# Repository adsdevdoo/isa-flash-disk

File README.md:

# ISA Flash Disk

8-битная ISA-карта с флеш-диском на микросхемах **Intel 28F008SA** для IBM PC XT, AT, 286, 386 и 486.
Цель — загрузка MS-DOS с карты и запись образа диска из DOS.

- 1 или 2 микросхемы PA28F008SA (PSOP-44) на карту: 1 или 2 Мбайт.
- Окно 8 Кбайт в верхней памяти + регистр банка в портах ввода-вывода.
- Собственный Option ROM: диск через INT 13h, загрузка DOS.
- Аппаратная защита от записи: без перемычки JP1 записать флеш невозможно.
- Логика 74HCT, без микроконтроллера.

## Статус

| Этап | Содержание | Состояние |
|---|---|---|
| 1. Исследование | документация, выбор архитектуры | выполнено |
| 2–3. Схема карты | 1–2 микросхемы, банки, защита записи | схема rev A: ERC 0, нетлист сверен |
| 5. Плата | разводка, DRC, Gerber | **rev B: DRC 0, соответствие схеме 0 расхождений**; от rev A отличается только шелкографией ([CHANGELOG](CHANGELOG.md)) |
| 2. Прототип | изготовление, чтение, адресация, запись | **rev A заказана в JLCPCB 2026-11-15** (5 шт., LeadFree HASL, фаска 45°), ещё не получена |
| 4. Программы | Option ROM, FLINFO/FLREAD/FLWRITE/FLFORMAT/FLTEST, mkdisk | **v1.2, чтение и запись из DOS, формат диска 3 (без потерь при сбое питания), проверка износа FLTEST: 136 проверок в эмуляторе, на железе нет** |

**Статус: инженерный прототип, не испытан в железе.** Заказана rev A, актуальная ревизия — rev B (та же медь, новая
шелкография). Плата 104.14 × 100 мм под планку Keystone 9202,
архив для JLCPCB — [hardware/gerber/](hardware/gerber/), параметры заказа и границы проверки —
[docs/manufacturing.md](docs/manufacturing.md). Схема — [docs/schematic.pdf](docs/schematic.pdf),
проект KiCad 9 — [hardware/kicad/](hardware/kicad/). Покупку и заказ выполняет владелец.

## Настройка переключателей

Переключатель в положении **ON = 0**, OFF = 1. Те же таблицы напечатаны на нижней стороне платы, у каждого
переключателя сверху подписан его бит адреса.

**SW1 — окно памяти 8 Кбайт** (SA19 = SA18 = 1 зашиты на плате)

| Окно | 1 (A13) | 2 (A14) | 3 (A15) | 4 (A16) | 5 (A17) |
|---|---|---|---|---|---|
| C8000h | ON | ON | OFF | ON | ON |
| **CC000h (по умолчанию)** | ON | OFF | OFF | ON | ON |
| D0000h | ON | ON | ON | OFF | ON |
| E0000h | ON | ON | ON | ON | OFF |

**SW2 — порты ввода-вывода** (8 портов; SA9 = 1 зашит, AEN = 0)

| Порты | 1 (A3) | 2 (A4) | 3 (A5) | 4 (A6) | 5 (A7) | 6 (A8) |
|---|---|---|---|---|---|---|
| 280h | ON | ON | ON | ON | OFF | ON |
| **2A0h (по умолчанию)** | ON | ON | OFF | ON | OFF | ON |
| 300h | ON | ON | ON | ON | ON | OFF |

Остальные адреса — по битам: окно C0000h…FE000h с шагом 8 Кбайт, порты 200h…3F8h с шагом 8
([docs/memory-map.md](docs/memory-map.md)). **JP1 WRITE** снята — флеш защищена от записи; ставится только на время
записи утилитами.

## Заказ платы в JLCPCB

Загрузить [hardware/gerber/isa-flash-disk-revB-jlcpcb.zip](hardware/gerber/isa-flash-disk-revB-jlcpcb.zip)
(rev A, заказанная 2026-11-15, лежит рядом без изменений) и выставить в форме:

| Поле | Значение |
|---|---|
| Base Material | FR-4 |
| Layers | 2 |
| Dimensions | 104.14 × 100 мм (определяется само) |
| Delivery Format | Single PCB |
| PCB Thickness | 1.6mm |
| Surface Finish | **LeadFree HASL** для прототипа (ламели лужёные) или **ENIG** (ламели золотые). Не OSP |
| Outer Copper Weight | 1 oz |
| Via Covering | Tented |
| Min via hole size/diameter | 0.3mm/(0.4/0.45mm) |
| Mark on PCB | Remove Mark |
| Gold Fingers | **Yes**, иначе не будет фаски |
| Beveling | **45°** |

Остальное — по умолчанию.

**Почему 45°, а не 30°:** при 30° фаска уходит на 1.13 мм от края (так пишет форма JLCPCB), а ламели
начинаются в 1.0 мм — фаска их заденет. После выбора 45° число d под картинкой должно быть меньше 1.0 мм.

Контур разъёма (выступ и уступы по бокам) уже есть в Gerber, отдельно его заказывать не нужно.

## Документация

| Файл | Что внутри |
|---|---|
| [docs/research.md](docs/research.md) | источники, находки, решения и открытые вопросы этапа 1 |
| [docs/intel-28f008sa.md](docs/intel-28f008sa.md) | характеристики микросхемы со ссылками на страницы даташита |
| [docs/original-module.md](docs/original-module.md) | исходный модуль и снятие микросхем |
| [docs/architecture.md](docs/architecture.md) | сравнение вариантов, выбранная схема, защита, VPP |
| [docs/isa-interface.md](docs/isa-interface.md) | шина ISA: контакты, циклы, питание, Option ROM |
| [docs/memory-map.md](docs/memory-map.md) | адреса окна и портов, регистры, разметка флеш |
| [docs/programming.md](docs/programming.md) | Option ROM, утилиты DOS, первая запись ПЗУ, запись на диск из DOS |
| [docs/testing.md](docs/testing.md) | замеры и проверки |
| [docs/assembly.md](docs/assembly.md) | сборка карты, детали с артикулами LCSC, распечатка платы 1:1 |
| [docs/manufacturing.md](docs/manufacturing.md) | заказ платы в JLCPCB, что проверено |
| [docs/models.md](docs/models.md) | 3D-модели и их ограничения |

Даташиты и руководства IBM лежат в [docs/datasheets/](docs/datasheets/) и [docs/references/](docs/references/).

## Структура

```
docs/          документация, даташиты, руководства
hardware/      kicad/, gerber/, bom/
firmware/      option-rom/ — Option ROM (NASM)
software/      dos/ — утилиты DOS (NASM)
tools/         вспомогательные скрипты для сборки и проверки
```

Документация на русском, исходный код и идентификаторы — на английском.
Рабочие правила проекта — [AGENTS.md](AGENTS.md).

## Лицензия

[MIT](LICENSE). Документы Intel, IBM, TI, AOS, onsemi, Keystone, Kingtek и FH в `docs/datasheets/` и `docs/references/` под эту
лицензию не подпадают и принадлежат их владельцам.

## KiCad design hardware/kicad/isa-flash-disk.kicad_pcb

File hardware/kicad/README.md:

# KiCad

Проект для **KiCad 9.0.2 или новее**: открыть `isa-flash-disk.kicad_pro`.

| Файл | Что это |
|---|---|
| `isa-flash-disk.kicad_sch` | схема rev A, один лист A2 |
| `isa_flash_disk.kicad_sym` | символ Intel 28F008SA (выводы PSOP-44 по DS, рис. 3) |
| `isa_flash_disk.pretty/` | все посадочные места проекта: PSOP-44 по чертежу Intel, ISA 8 бит, копии стандартных KiCad 9 |
| `expected-nets.json` | таблица соединений, из которой построена схема |
| `isa-flash-disk.kicad_pcb` | плата rev B: 104.14 × 100 мм, 2 слоя, разведена, земля залита с двух сторон. Медь как у rev A, изменена шелкография ([CHANGELOG](../../CHANGELOG.md)) |
| `3d/` | 3D-модели всех деталей (копии из KiCad 9.0.2, [docs/models.md](../../docs/models.md)) |
| `reports/erc.rpt` | последний отчёт ERC |
| `reports/netlist-check.txt` | сверка нетлиста с `expected-nets.json` |
| `reports/drc.rpt` | последний DRC платы с проверкой соответствия схеме |

Статус: **схема rev A, плата rev B: ERC 0, DRC 0, соответствие схеме и плате без расхождений. В железе не
проверялось.** PDF схемы — [docs/schematic.pdf](../../docs/schematic.pdf), заказ — [docs/manufacturing.md](../../docs/manufacturing.md).

## Как схема получена

Rev A сгенерирована скриптами:

```bash
python tools/kicad/gen_footprints.py
```

```bash
python tools/kicad/gen_schematic.py
```

Генератор соединяет выводы короткими проводниками с метками цепей, поэтому схема читается как таблица
соединений. Дальше её можно править в KiCad. Генератор не перезапишет схему, изменённую вручную
(сверяет SHA-256 с `.generated.sha256`); `--force` отбрасывает ручные правки.

## Как получена плата

Плата строится в три шага, как в retro535 (размещение скриптом, трассировка FreeRouting, доводка скриптом):

```bash
"C:/Program Files/KiCad/9.0/bin/python.exe" tools/kicad/make_board.py
```

```bash
java -jar freerouting-2.5.0.jar -de hardware/kicad/build/placed.dsn -do hardware/kicad/build/placed.ses -mp 100 --gui.enabled=false
```

```bash
"C:/Program Files/KiCad/9.0/bin/python.exe" tools/kicad/route_board.py
```

- `make_board.py` берёт нетлист из схемы, ставит контур (геометрия под планку Keystone 9202), ламели,
  отверстия под планку, детали, запретную зону на ламелях и зафиксированные отводы от ламелей в тело платы;
  результат — `build/placed.kicad_pcb` и `build/placed.dsn` (папка `build/` не коммитится).
- FreeRouting 2.5.0 — внешний автотрассировщик (github.com/freerouting/freerouting), в репозиторий не входит.
- `route_board.py` импортирует трассировку, заливает землю с двух сторон, добавляет шелкографию и сохраняет
  `isa-flash-disk.kicad_pcb`, переносит правила в `isa-flash-disk.kicad_pro`. Плату, изменённую в KiCad,
  без `--force` не перезаписывает (`.generated-pcb.sha256`).
- Шелкография задана только в `silk_board.py`. `route_board.py` вызывает его до сшивки земли, чтобы
  переходные не попадали под надписи. Отдельно он перерисовывает шелкографию готовой платы, медь не меняет;
  повторный запуск даёт тот же файл:

```bash
"C:/Program Files/KiCad/9.0/bin/python.exe" tools/kicad/silk_board.py
```

  Скрипт ставит обозначения, тип микросхем, транзисторов и резисторных сборок, функциональные подписи,
  нижний информационный блок и таблицы переключателей. Надпись без свободного места или ближе 0.2 мм к
  площадке, 0.15 мм к другой шелкографии — ошибка, а не наложение.

## Проверка после изменений

```bash
kicad-cli sch erc --format report --severity-all -o hardware/kicad/reports/erc.rpt hardware/kicad/isa-flash-disk.kicad_sch
```

```bash
kicad-cli sch export netlist --format kicadsexpr -o netlist.net hardware/kicad/isa-flash-disk.kicad_sch
```

```bash
python tools/kicad/check_netlist.py netlist.net
```

Нетлист содержит абсолютные локальные пути, в репозиторий его не класть.

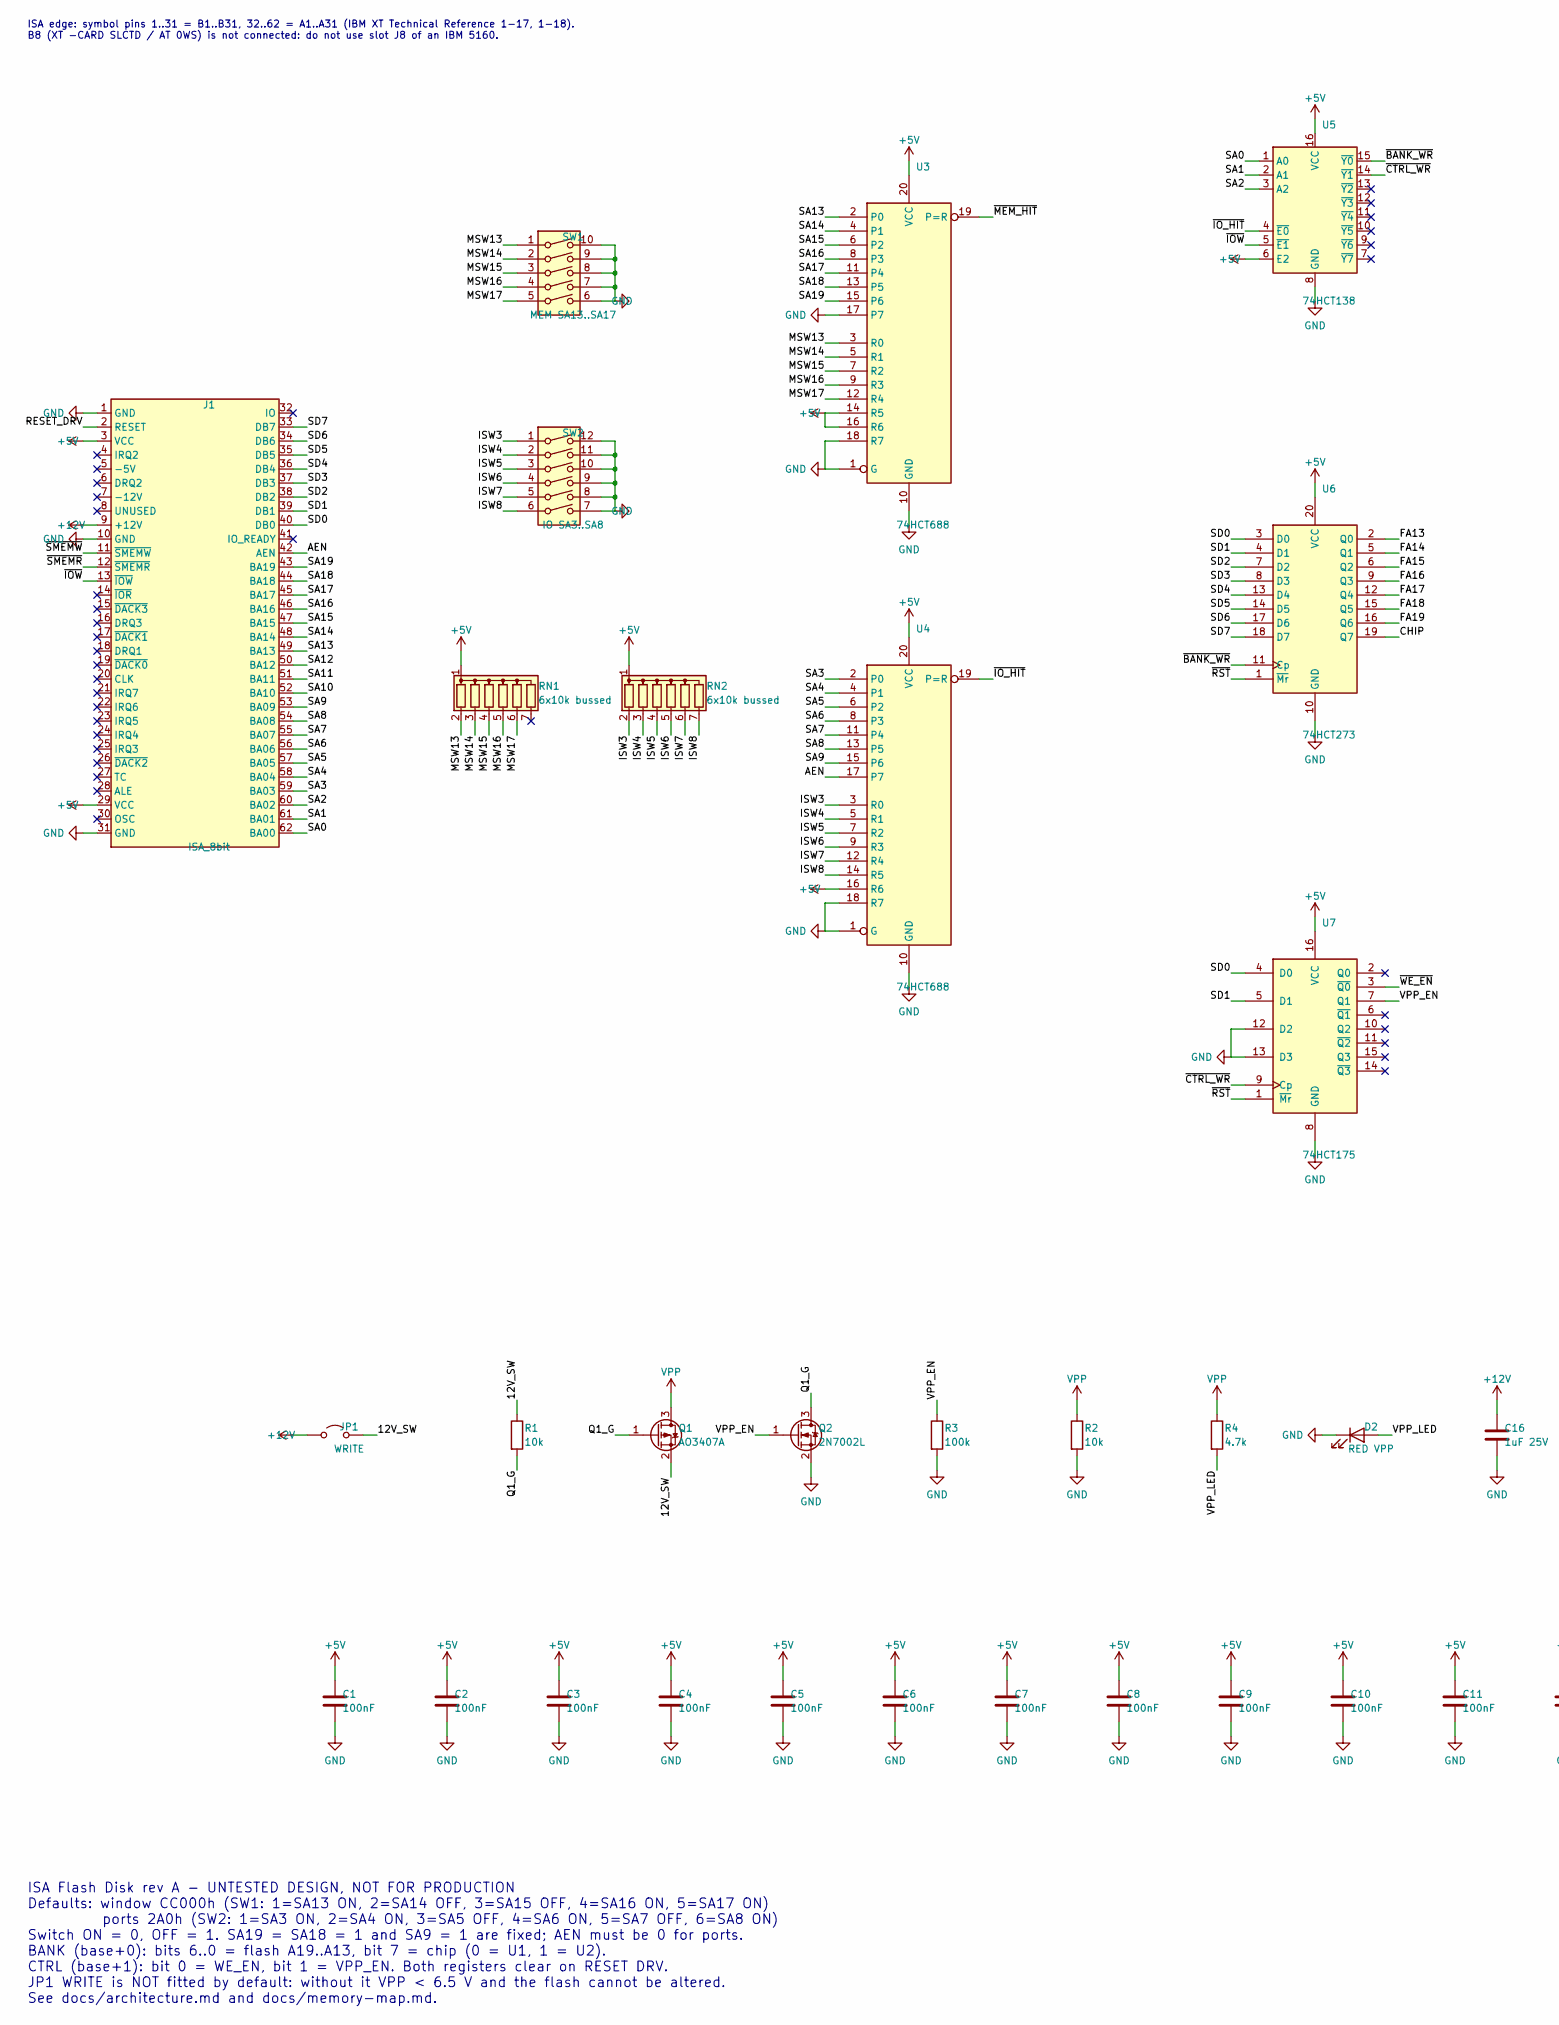
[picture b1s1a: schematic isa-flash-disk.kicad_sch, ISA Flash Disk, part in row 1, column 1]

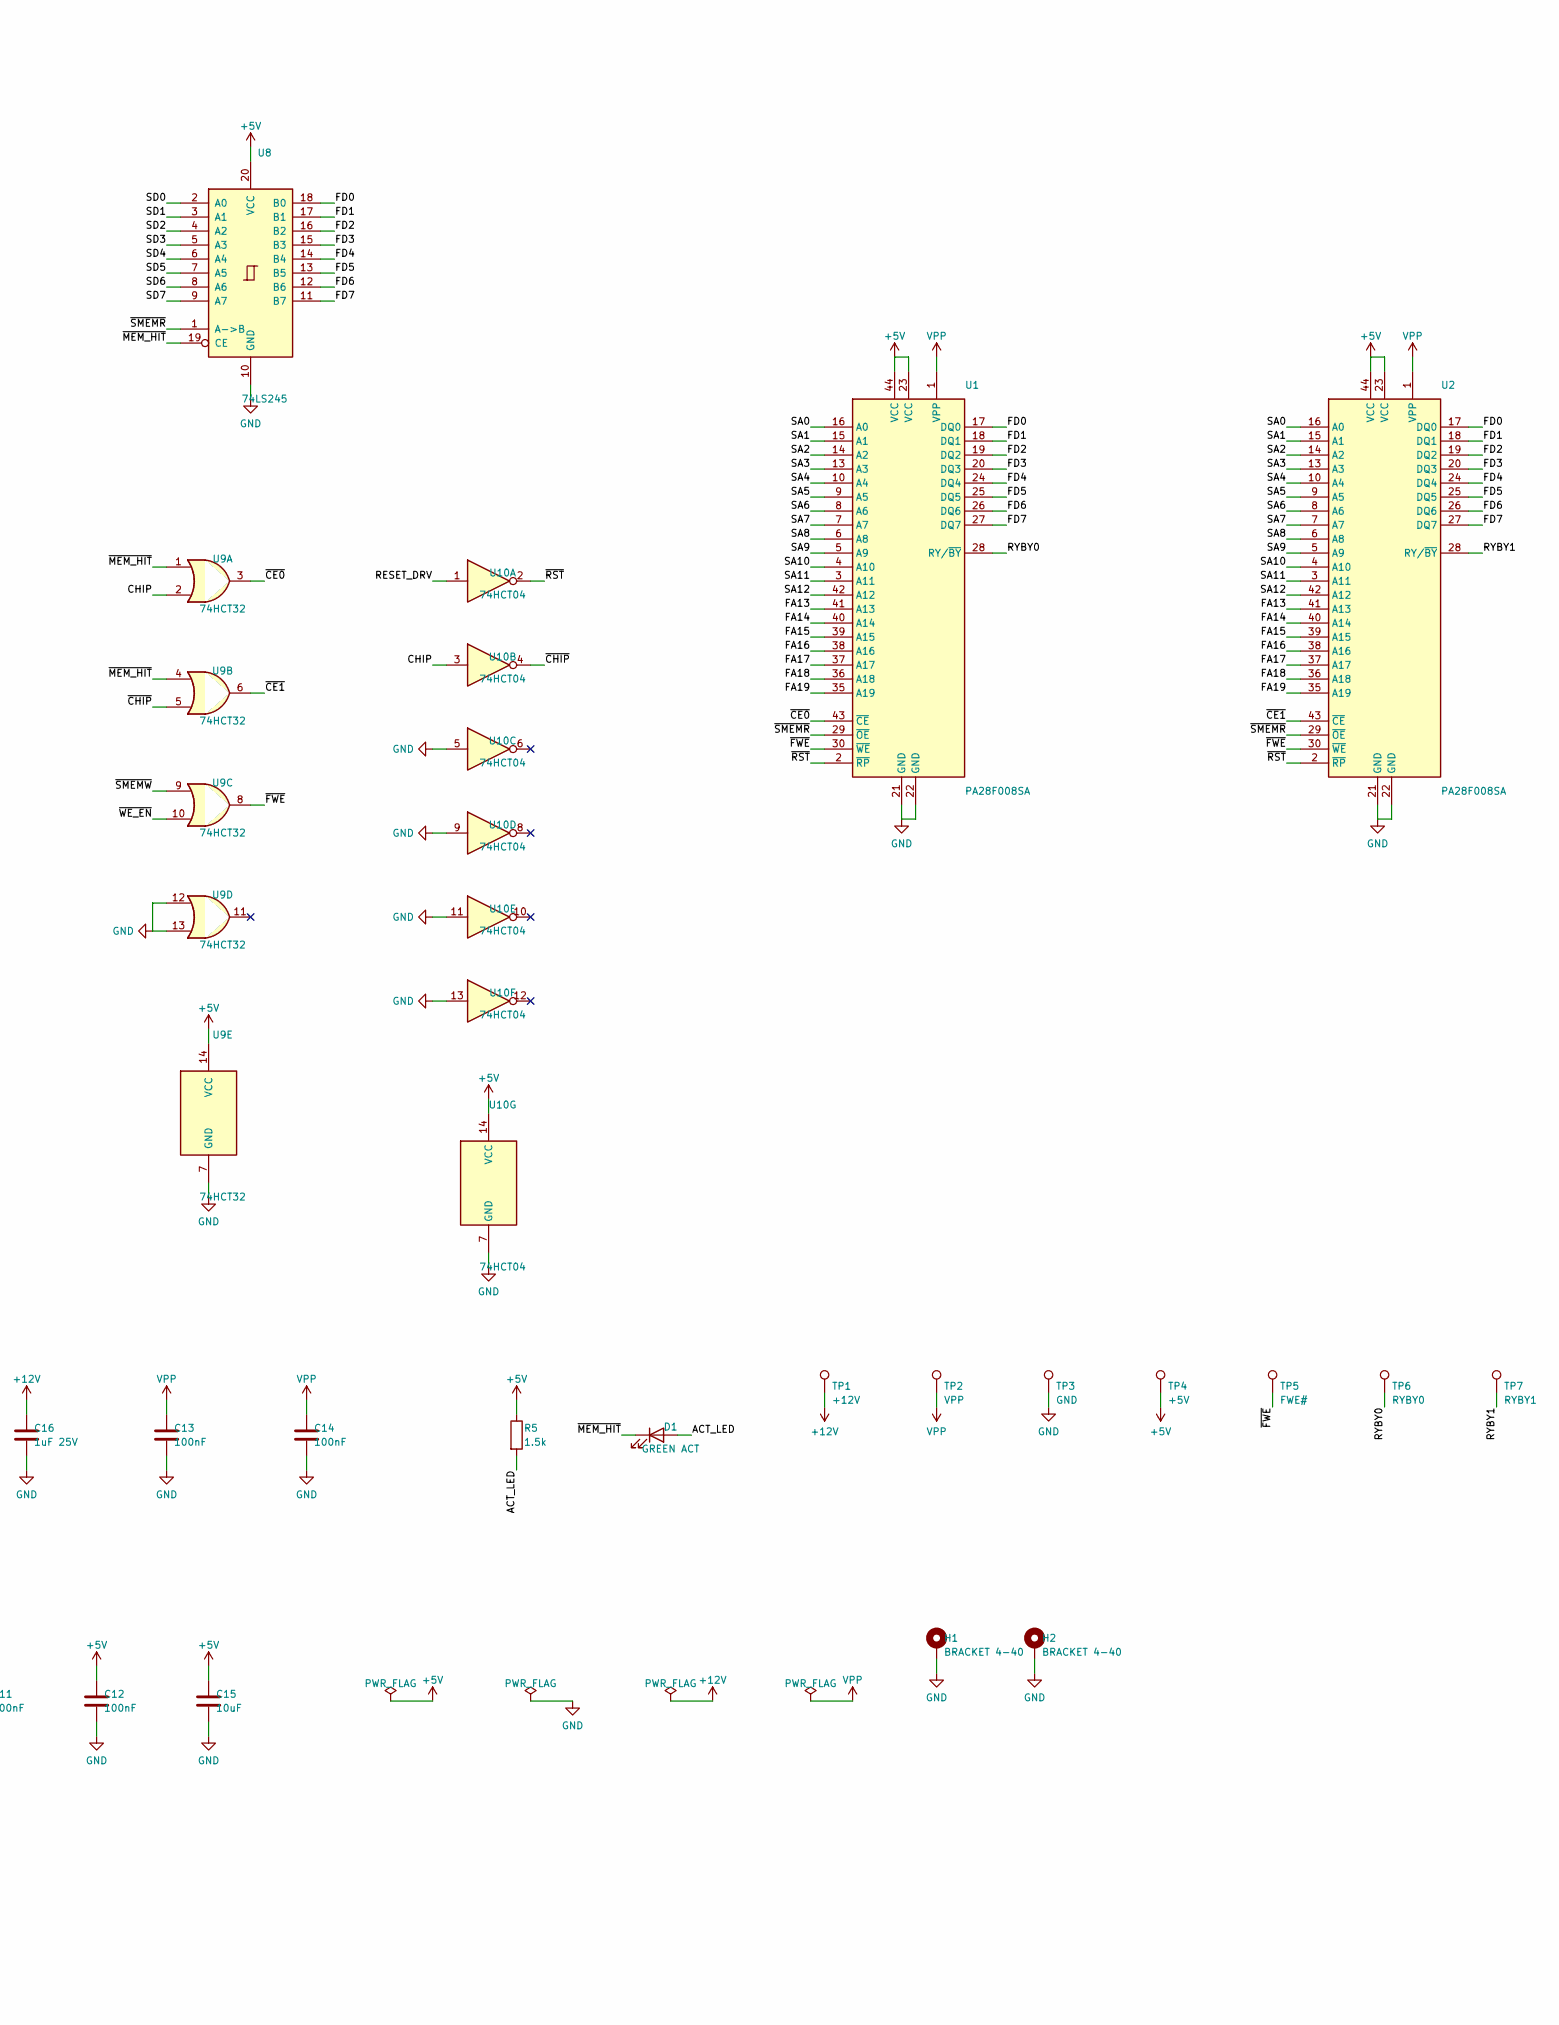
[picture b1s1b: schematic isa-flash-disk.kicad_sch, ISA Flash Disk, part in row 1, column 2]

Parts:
C1, C2, C3, C4, C5, C6, C7, C8, C9, C10, C11, C12, C13, C14: 100nF; C_0805_2012Metric_Pad1.18x1.45mm_HandSolder
C15: 10uF; C_0805_2012Metric_Pad1.18x1.45mm_HandSolder
C16: 1uF 25V; C_0805_2012Metric_Pad1.18x1.45mm_HandSolder
D1: GREEN ACT; LED_0805_2012Metric_Pad1.15x1.40mm_HandSolder
D2: RED VPP; LED_0805_2012Metric_Pad1.15x1.40mm_HandSolder
H1, H2: BRACKET 4-40; MountingHole_3.2mm_Pad5.0mm
J1: ISA_8bit; ISA_8bit_Edge
JP1: WRITE; PinHeader_1x02_P2.54mm_Vertical
Q1: AO3407A; SOT-23; MPN AO3407A
Q2: 2N7002L; SOT-23; MPN 2N7002LT1G
R1, R2: 10k; R_0805_2012Metric_Pad1.20x1.40mm_HandSolder
R3: 100k; R_0805_2012Metric_Pad1.20x1.40mm_HandSolder
R4: 4.7k; R_0805_2012Metric_Pad1.20x1.40mm_HandSolder
R5: 1.5k; R_0805_2012Metric_Pad1.20x1.40mm_HandSolder
RN1, RN2: 6x10k bussed; R_Array_SIP7
SW1: MEM SA13..SA17; SW_DIP_SPSTx05_Slide_9.78x14.88mm_W7.62mm_P2.54mm
SW2: IO SA3..SA8; SW_DIP_SPSTx06_Slide_9.78x17.42mm_W7.62mm_P2.54mm
TP1: +12V; TestPoint_THTPad_D2.0mm_Drill1.0mm
TP2: VPP; TestPoint_THTPad_D2.0mm_Drill1.0mm
TP3: GND; TestPoint_THTPad_D2.0mm_Drill1.0mm
TP4: +5V; TestPoint_THTPad_D2.0mm_Drill1.0mm
TP5: FWE#; TestPoint_THTPad_D2.0mm_Drill1.0mm
TP6: RYBY0; TestPoint_THTPad_D2.0mm_Drill1.0mm
TP7: RYBY1; TestPoint_THTPad_D2.0mm_Drill1.0mm
U1, U2: PA28F008SA; Intel_PSOP-44_P1.27mm; MPN PA28F008SA-85 / -120 (salvaged)
U3, U4: 74HCT688; SOIC-20W_7.5x12.8mm_P1.27mm; MPN CD74HCT688M96
U5: 74HCT138; SOIC-16_3.9x9.9mm_P1.27mm; MPN SN74HCT138DR
U6: 74HCT273; SOIC-20W_7.5x12.8mm_P1.27mm; MPN SN74HCT273DWR
U7: 74HCT175; SOIC-16_3.9x9.9mm_P1.27mm; MPN CD74HCT175M96
U8: 74LS245; SOIC-20W_7.5x12.8mm_P1.27mm; MPN SN74LS245DWR
U9: 74HCT32; SOIC-14_3.9x8.7mm_P1.27mm; MPN SN74HCT32DR
U10: 74HCT04; SOIC-14_3.9x8.7mm_P1.27mm; MPN SN74HCT04DR

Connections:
+5V: C1.1, C2.1, C3.1, C4.1, C5.1, C6.1, C7.1, C8.1, C9.1, C10.1, C11.1, C12.1, C15.1, J1.3 (VCC), J1.29 (VCC), R5.1, RN1.1 (common), RN2.1 (common), TP4.1, U1.23 (VCC), U1.44 (VCC), U2.23 (VCC), U2.44 (VCC), U3.14 (R5), U3.16 (R6), U3.20 (VCC), U4.16 (R6), U4.20 (VCC), U5.6 (E2), U5.16 (VCC), U6.20 (VCC), U7.16 (VCC), U8.20 (VCC), U9.14 (VCC), U10.14 (VCC)
+12V: C16.1, J1.9 (+12V), JP1.1 (A), TP1.1
/12V_SW: JP1.2 (B), Q1.2 (S), R1.1
/ACT_LED: D1.2 (A), R5.2
/AEN: J1.42 (AEN), U4.17 (P7)
/CHIP: U6.19 (Q7), U9.2, U10.3
/FA13: U1.41 (A13), U2.41 (A13), U6.2 (Q0)
/FA14: U1.40 (A14), U2.40 (A14), U6.5 (Q1)
/FA15: U1.39 (A15), U2.39 (A15), U6.6 (Q2)
/FA16: U1.38 (A16), U2.38 (A16), U6.9 (Q3)
/FA17: U1.37 (A17), U2.37 (A17), U6.12 (Q4)
/FA18: U1.36 (A18), U2.36 (A18), U6.15 (Q5)
/FA19: U1.35 (A19), U2.35 (A19), U6.16 (Q6)
/FD0: U1.17 (DQ0), U2.17 (DQ0), U8.18 (B0)
/FD1: U1.18 (DQ1), U2.18 (DQ1), U8.17 (B1)
/FD2: U1.19 (DQ2), U2.19 (DQ2), U8.16 (B2)
/FD3: U1.20 (DQ3), U2.20 (DQ3), U8.15 (B3)
/FD4: U1.24 (DQ4), U2.24 (DQ4), U8.14 (B4)
/FD5: U1.25 (DQ5), U2.25 (DQ5), U8.13 (B5)
/FD6: U1.26 (DQ6), U2.26 (DQ6), U8.12 (B6)
/FD7: U1.27 (DQ7), U2.27 (DQ7), U8.11 (B7)
/ISW3: RN2.2 (R1), SW2.1, U4.3 (R0)
/ISW4: RN2.3 (R2), SW2.2, U4.5 (R1)
/ISW5: RN2.4 (R3), SW2.3, U4.7 (R2)
/ISW6: RN2.5 (R4), SW2.4, U4.9 (R3)
/ISW7: RN2.6 (R5), SW2.5, U4.12 (R4)
/ISW8: RN2.7 (R6), SW2.6, U4.14 (R5)
/MSW13: RN1.2 (R1), SW1.1, U3.3 (R0)
/MSW14: RN1.3 (R2), SW1.2, U3.5 (R1)
/MSW15: RN1.4 (R3), SW1.3, U3.7 (R2)
/MSW16: RN1.5 (R4), SW1.4, U3.9 (R3)
/MSW17: RN1.6 (R5), SW1.5, U3.12 (R4)
/Q1_G: Q1.1 (G), Q2.3 (D), R1.2
/RESET_DRV: J1.2 (RESET), U10.1
/RYBY0: TP6.1, U1.28 (RY/~BY)
/RYBY1: TP7.1, U2.28 (RY/~BY)
/SA0: J1.62 (BA00), U1.16 (A0), U2.16 (A0), U5.1 (A0)
/SA1: J1.61 (BA01), U1.15 (A1), U2.15 (A1), U5.2 (A1)
/SA2: J1.60 (BA02), U1.14 (A2), U2.14 (A2), U5.3 (A2)
/SA3: J1.59 (BA03), U1.13 (A3), U2.13 (A3), U4.2 (P0)
/SA4: J1.58 (BA04), U1.10 (A4), U2.10 (A4), U4.4 (P1)
/SA5: J1.57 (BA05), U1.9 (A5), U2.9 (A5), U4.6 (P2)
/SA6: J1.56 (BA06), U1.8 (A6), U2.8 (A6), U4.8 (P3)
/SA7: J1.55 (BA07), U1.7 (A7), U2.7 (A7), U4.11 (P4)
/SA8: J1.54 (BA08), U1.6 (A8), U2.6 (A8), U4.13 (P5)
/SA9: J1.53 (BA09), U1.5 (A9), U2.5 (A9), U4.15 (P6)
/SA10: J1.52 (BA10), U1.4 (A10), U2.4 (A10)
/SA11: J1.51 (BA11), U1.3 (A11), U2.3 (A11)
/SA12: J1.50 (BA12), U1.42 (A12), U2.42 (A12)
/SA13: J1.49 (BA13), U3.2 (P0)
/SA14: J1.48 (BA14), U3.4 (P1)
/SA15: J1.47 (BA15), U3.6 (P2)
/SA16: J1.46 (BA16), U3.8 (P3)
/SA17: J1.45 (BA17), U3.11 (P4)
/SA18: J1.44 (BA18), U3.13 (P5)
/SA19: J1.43 (BA19), U3.15 (P6)
/SD0: J1.40 (DB0), U6.3 (D0), U7.4 (D0), U8.2 (A0)
/SD1: J1.39 (DB1), U6.4 (D1), U7.5 (D1), U8.3 (A1)
/SD2: J1.38 (DB2), U6.7 (D2), U8.4 (A2)
/SD3: J1.37 (DB3), U6.8 (D3), U8.5 (A3)
/SD4: J1.36 (DB4), U6.13 (D4), U8.6 (A4)
/SD5: J1.35 (DB5), U6.14 (D5), U8.7 (A5)
/SD6: J1.34 (DB6), U6.17 (D6), U8.8 (A6)
/SD7: J1.33 (DB7), U6.18 (D7), U8.9 (A7)
/VPP_EN: Q2.1 (G), R3.1, U7.7 (Q1)
/VPP_LED: D2.2 (A), R4.2
/~BANK_WR: U5.15 (~Y0), U6.11 (Cp)
/~CE0: U1.43 (~CE), U9.3
/~CE1: U2.43 (~CE), U9.6
/~CHIP: U9.5, U10.4
/~CTRL_WR: U5.14 (~Y1), U7.9 (Cp)
/~FWE: TP5.1, U1.30 (~WE), U2.30 (~WE), U9.8
/~IOW: J1.13 (~IOW), U5.5 (~E1)
/~IO_HIT: U4.19 (P=R), U5.4 (~E0)
/~MEM_HIT: D1.1 (K), U3.19 (P=R), U8.19 (CE), U9.1, U9.4
/~RST: U1.2 (~RP), U2.2 (~RP), U6.1 (~Mr), U7.1 (~Mr), U10.2
/~SMEMR: J1.12 (~SMEMR), U1.29 (~OE), U2.29 (~OE), U8.1 (A->B)
/~SMEMW: J1.11 (~SMEMW), U9.9
/~WE_EN: U7.3 (~Q0), U9.10
GND: C1.2, C2.2, C3.2, C4.2, C5.2, C6.2, C7.2, C8.2, C9.2, C10.2, C11.2, C12.2, C13.2, C14.2, C15.2, C16.2, D2.1 (K), H1.1, H2.1, J1.1 (GND), J1.10 (GND), J1.31 (GND), Q2.2 (S), R2.2, R3.2, SW1.6, SW1.7, SW1.8, SW1.9, SW1.10, SW2.7, SW2.8, SW2.9, SW2.10, SW2.11, SW2.12, TP3.1, U1.21 (GND), U1.22 (GND), U2.21 (GND), U2.22 (GND), U3.1 (G), U3.10 (GND), U3.17 (P7), U3.18 (R7), U4.1 (G), U4.10 (GND), U4.18 (R7), U5.8 (GND), U6.10 (GND), U7.8 (GND), U7.12 (D2), U7.13 (D3), U8.10 (GND), U9.7 (GND), U9.12, U9.13, U10.5, U10.7 (GND), U10.9, U10.11, U10.13
VPP: C13.1, C14.1, Q1.3 (D), R2.1, R4.1, TP2.1, U1.1 (VPP), U2.1 (VPP)

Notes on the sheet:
ISA Flash Disk rev A - UNTESTED DESIGN, NOT FOR PRODUCTION Defaults: window CC000h (SW1: 1=SA13 ON, 2=SA14 OFF, 3=SA15 OFF, 4=SA16 ON, 5=SA17 ON) ports 2A0h (SW2: 1=SA3 ON, 2=SA4 ON, 3=SA5 OFF, 4=SA6 ON, 5=SA7 OFF, 6=SA8 ON) Switch ON = 0, OFF = 1. SA19 = SA18 = 1 and SA9 = 1 are fixed; AEN must be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
ISA edge: symbol pins 1..31 = B1..B31, 32..62 = A1..A31 (IBM XT Technical Reference 1-17, 1-18). B8 (XT -CARD SLCTD / AT 0WS) is not connected: do not use slot J8 of an IBM 5160.

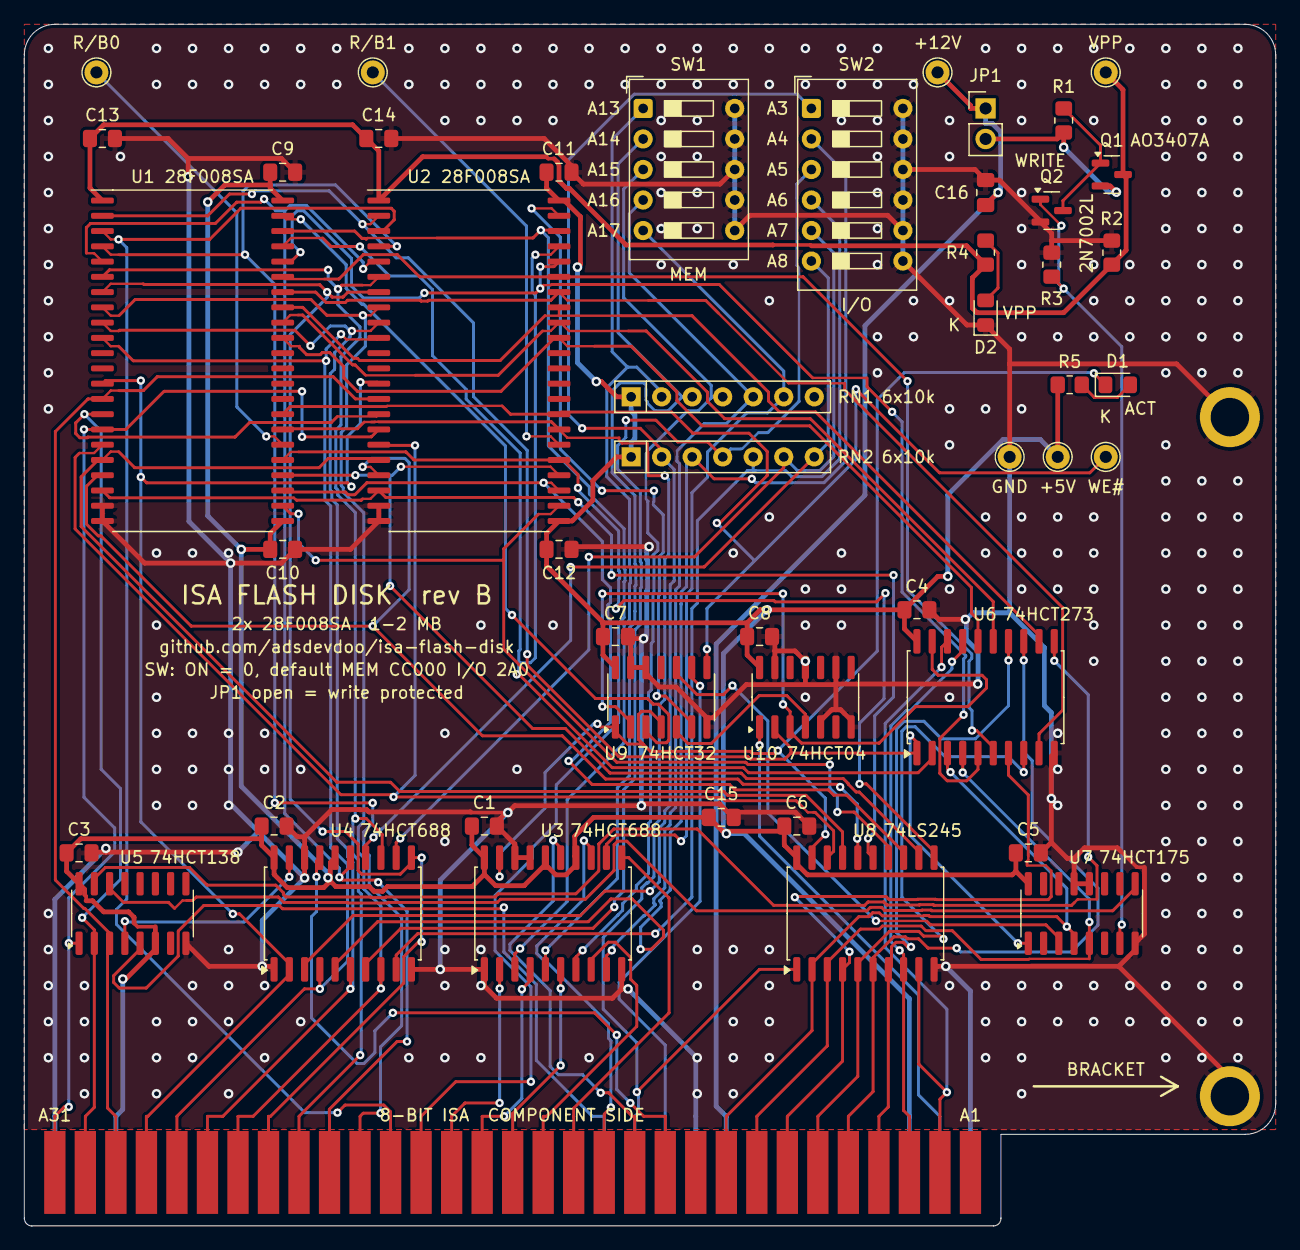
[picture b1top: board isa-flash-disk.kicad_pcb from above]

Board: 2 copper layers, 104.1 x 100.0 mm, 50 parts (0 on the bottom side), 81 nets.

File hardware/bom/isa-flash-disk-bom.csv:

"Reference","Value","Footprint","MPN","Qty","Datasheet"
"C1-C14","100nF","isa_flash_disk:C_0805_2012Metric_Pad1.18x1.45mm_HandSolder","","14",""
"C15","10uF","isa_flash_disk:C_0805_2012Metric_Pad1.18x1.45mm_HandSolder","","1",""
"C16","1uF 25V","isa_flash_disk:C_0805_2012Metric_Pad1.18x1.45mm_HandSolder","","1",""
"D1","GREEN ACT","isa_flash_disk:LED_0805_2012Metric_Pad1.15x1.40mm_HandSolder","","1",""
"D2","RED VPP","isa_flash_disk:LED_0805_2012Metric_Pad1.15x1.40mm_HandSolder","","1",""
"JP1","WRITE","isa_flash_disk:PinHeader_1x02_P2.54mm_Vertical","","1",""
"Q1","AO3407A","isa_flash_disk:SOT-23","AO3407A","1","docs/datasheets/aos-ao3407a.pdf"
"Q2","2N7002L","isa_flash_disk:SOT-23","2N7002LT1G","1","docs/datasheets/onsemi-2n7002l.pdf"
"R1,R2","10k","isa_flash_disk:R_0805_2012Metric_Pad1.20x1.40mm_HandSolder","","2",""
"R3","100k","isa_flash_disk:R_0805_2012Metric_Pad1.20x1.40mm_HandSolder","","1",""
"R4","4.7k","isa_flash_disk:R_0805_2012Metric_Pad1.20x1.40mm_HandSolder","","1",""
"R5","1.5k","isa_flash_disk:R_0805_2012Metric_Pad1.20x1.40mm_HandSolder","","1",""
"RN1,RN2","6x10k bussed","isa_flash_disk:R_Array_SIP7","","2",""
"SW1","MEM SA13..SA17","isa_flash_disk:SW_DIP_SPSTx05_Slide_9.78x14.88mm_W7.62mm_P2.54mm","","1",""
"SW2","IO SA3..SA8","isa_flash_disk:SW_DIP_SPSTx06_Slide_9.78x17.42mm_W7.62mm_P2.54mm","","1",""
"U1,U2","PA28F008SA","isa_flash_disk:Intel_PSOP-44_P1.27mm","PA28F008SA-85 / -120 (salvaged)","2","docs/datasheets/intel-28f008sa-290429-008.pdf"
"U3,U4","74HCT688","isa_flash_disk:SOIC-20W_7.5x12.8mm_P1.27mm","CD74HCT688M96","2","docs/datasheets/ti-cd74hct688.pdf"
"U5","74HCT138","isa_flash_disk:SOIC-16_3.9x9.9mm_P1.27mm","SN74HCT138DR","1","docs/datasheets/ti-sn74hct138.pdf"
"U6","74HCT273","isa_flash_disk:SOIC-20W_7.5x12.8mm_P1.27mm","SN74HCT273DWR","1","docs/datasheets/ti-sn74hct273.pdf"
"U7","74HCT175","isa_flash_disk:SOIC-16_3.9x9.9mm_P1.27mm","CD74HCT175M96","1","docs/datasheets/ti-cd74hct175.pdf"
"U8","74LS245","isa_flash_disk:SOIC-20W_7.5x12.8mm_P1.27mm","SN74LS245DWR","1","docs/datasheets/ti-sn74ls245.pdf"
"U9","74HCT32","isa_flash_disk:SOIC-14_3.9x8.7mm_P1.27mm","SN74HCT32DR","1","docs/datasheets/ti-sn74hct32.pdf"
"U10","74HCT04","isa_flash_disk:SOIC-14_3.9x8.7mm_P1.27mm","SN74HCT04DR","1","docs/datasheets/ti-sn74hct04.pdf"
